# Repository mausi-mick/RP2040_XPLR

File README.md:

VL53L0X 360° Radar mit RP2040 auf Experimentierboard

Aufgebaut habe ich das „Radar" auf einem von mir entwickelten Experimentierboard für den RP2040 bzw. RP2350 im Format 100 x 160:

Auf dem Board - neben dem PICO-Board - können folgende Komponeneten eingesteckt werden :

    SPI - (Touch) - Displays mit ILI9341 Treiber von 2.4 bis 3.2 Zoll (240 x 320 Pixel)

                         und mit ST7736 Treiber      3.5 und 4 Zoll   (320 x 480 Pixel)

    Dual DAC MCP48x2 (8/10/12 bit) (SPI)
    Quad ADC MCP3x04 (10/12 bit)   (SPI)
    EEPROM 24LC64/256 (I2C)
    bis zu vier Encoder bzw. Potis
    vier Taster
    vier Steckplätze für LEDs

obige Komponenten sind auf Buchsen (Pinheader) steckbar.

Ausserdem ist das Boardmit einem kleinen Breadboard bestückt.

Die Stromversorgung erfolgt momentan über die USB-Buchse des Picos,
eine zusätzliche ist auf dem Board integrierbar (USBC) (-5V/60mA, 12V (ca 2A ).

Um möglichst viele dieser Komponenten zu testen, hab ich dieses Radar auf dem Board aufgebaut.

Es besteht aus zwei VL53L0X, die mit der Rückseite zueinander auf einem kleinen Servo (SG90?) befestigt sind.

Den Drehwinkel kann man mit der Software in geringen Grenzen ändern (hier: auf 180° justieren).

Das Programm ist in der Arduino IDE (2.34) erstellt.

Für die Grafik verwende ich die hervorragende Bibliothek TFT_eSPI von H. Bodmer,

für die Distanzsensoren die Bibliothek VL53L0X.h von Pololu.

Am Anfang läuft nur in rasendem Tempo der Grafik - Test ab.

Anschliessend wird der kreisförmige Radar-Bildschirm mit den Koordinaten angezeigt. Die Distanz-Sensoren nehmen ihre Arbeit auf und das Servo dreht sich von 0° - 180° und zurück...

Die Auflösung (maximale Entfernungsanzeige ) der Graphik lässt sich mit dem Drehencoder in

Stufen von 500 mm, 1000mm, 1500 mm und 2000 mm einstellen.

Löschung des Bildschirms geschieht über den RUN (=Reset)-Pin des Pico über Taster S2.

Das Programm und die Platinen-Layouts (KiCad) werden auf Github gestellt. Es gibt auch ein

kleines KiCad-Projekt zur Beschriftung der PICO-Pins (zum Aufkleben auf dem PICO ) :

{width="17cm" height="6.93cm"}

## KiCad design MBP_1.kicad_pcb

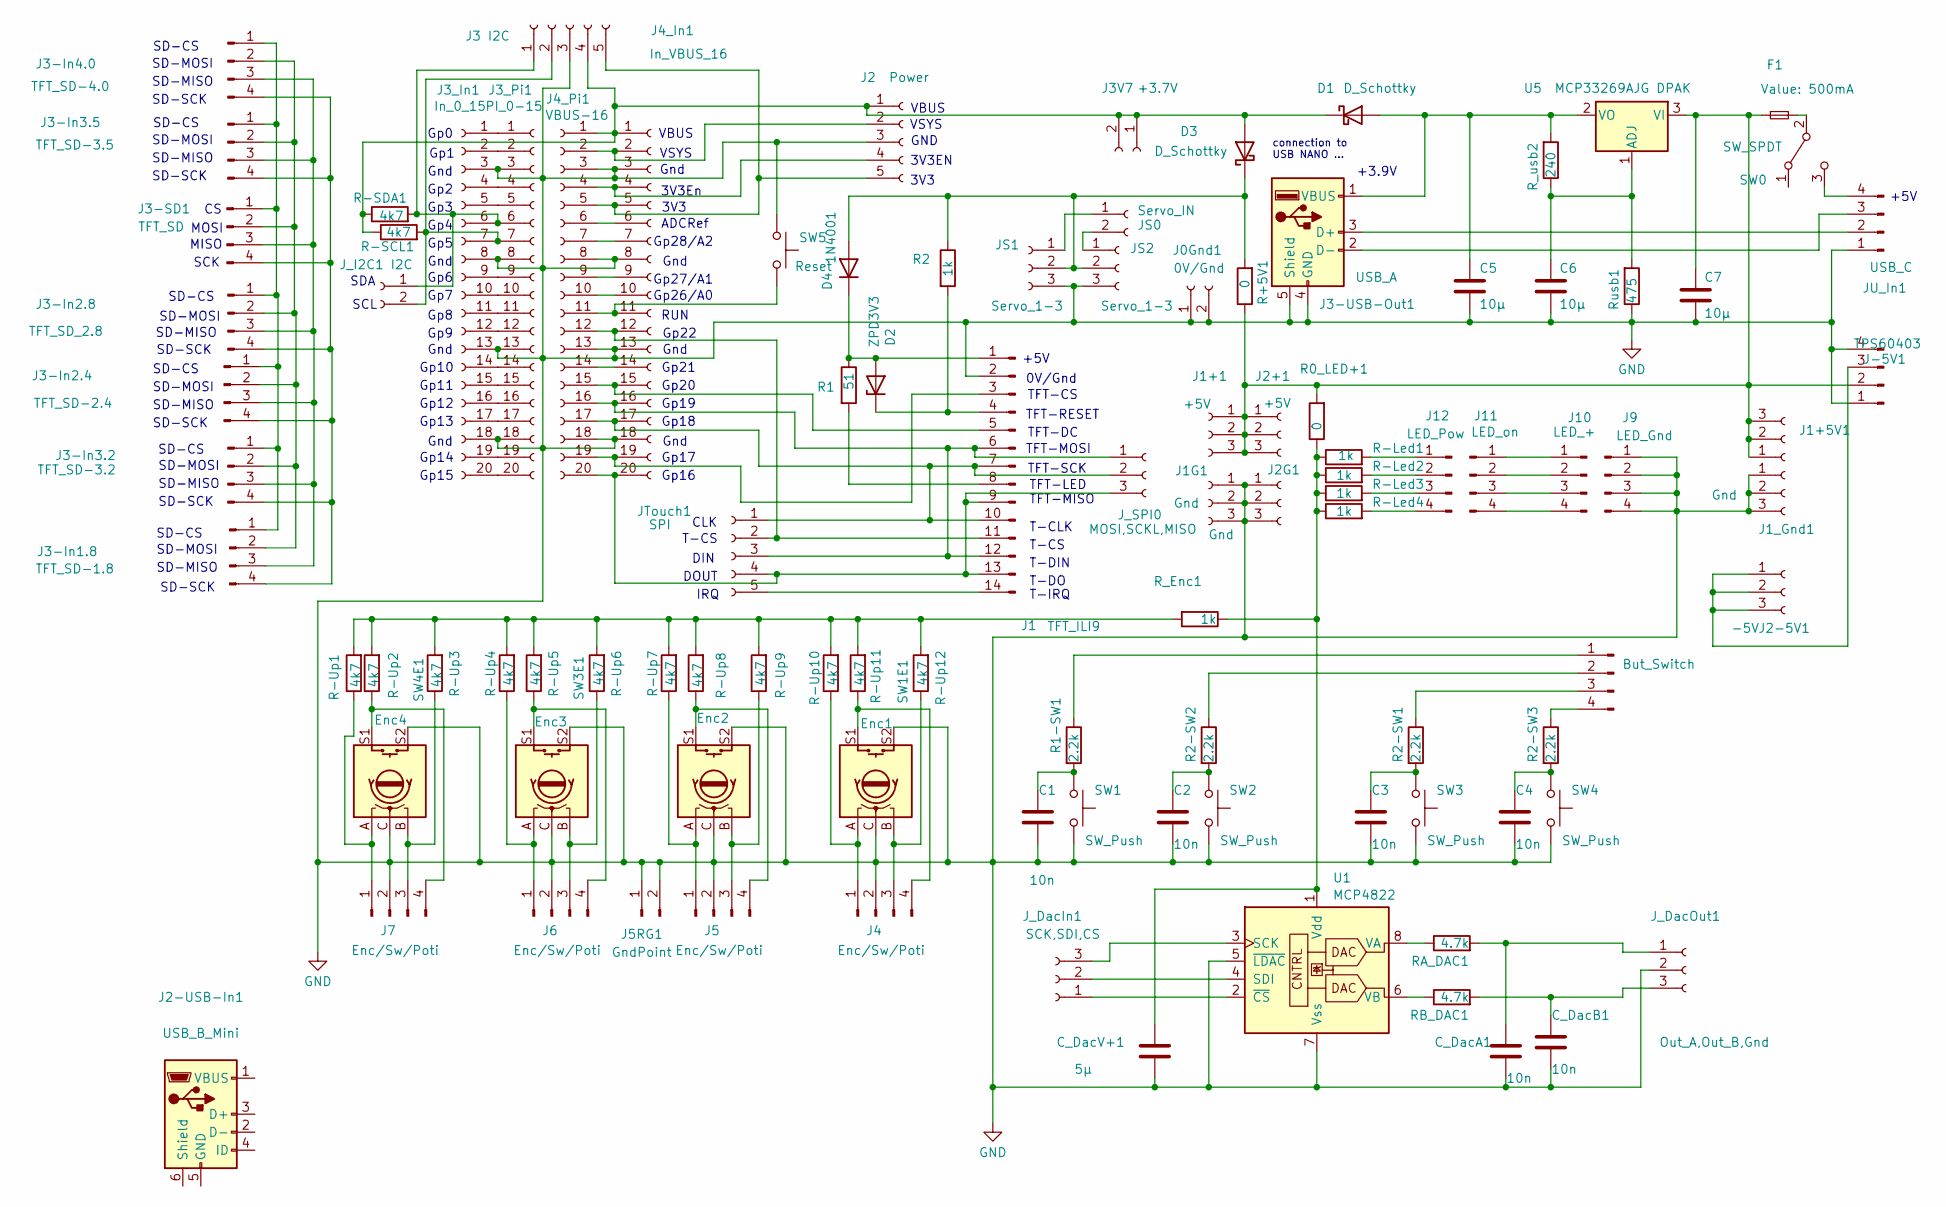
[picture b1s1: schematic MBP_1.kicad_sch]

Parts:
C1, C2, C3, C4: 10n; C_1206_3216Metric_Pad1.33x1.80mm_HandSolder
C5, C6, C7: 10µ; C_1812_4532Metric_Pad1.57x3.40mm_HandSolder
C_DacA1: 10n; C_1206_3216Metric_Pad1.33x1.80mm_HandSolder
C_DacB1: 10n; C_1206_3216Metric_Pad1.33x1.80mm_HandSolder
C_DacV+1: 5µ; C_1812_4532Metric_Pad1.57x3.40mm_HandSolder
D1: D_Schottky; D_DO-15_P15.24mm_Horizontal
D2: ZPD3V3; D_DO-35_SOD27_P10.16mm_Horizontal
D3: D_Schottky; D_DO-15_P12.70mm_Horizontal
D4: 1N4001; D_2010_5025Metric_Pad1.52x2.65mm_HandSolder
F1: 500mA; Fuse_2010_5025Metric_Pad1.52x2.65mm_HandSolder
J0Gnd1: 0V/Gnd; PinHeader_1x02_P2.54mm_Vertical
J1: TFT_ILI9; PinHeader_1x14_P2.54mm_Vertical
J1+1, J1+5V1, J2+1: +5V; PinHeader_1x03_P2.54mm_Vertical
J1G1, J1_Gnd1, J2G1: Gnd; PinHeader_1x03_P2.54mm_Vertical
J2: Power; PinSocket_1x05_P2.54mm_Vertical
J2-5V1: -5V; PinHeader_1x03_P2.54mm_Vertical
J2-USB-In1: USB_B_Mini; USB_Mini-B_Wuerth_65100516121_Horizontal
J3: I2C; PinSocket_1x05_P2.54mm_Vertical
J3-In1.8: TFT_SD-1.8; PinHeader_1x04_P2.54mm_Vertical
J3-In2.4: TFT_SD-2.4; PinHeader_1x04_P2.54mm_Vertical
J3-In2.8: TFT_SD_2.8; PinSocket_1x04_P2.54mm_Vertical
J3-In3.2: TFT_SD-3.2; PinHeader_1x04_P2.54mm_Vertical
J3-In3.5: TFT_SD-3.5; PinHeader_1x04_P2.54mm_Vertical
J3-In4.0: TFT_SD-4.0; PinHeader_1x04_P2.54mm_Vertical
J3-SD1: TFT_SD; PinHeader_1x04_P2.54mm_Horizontal
J3-USB-Out1: USB_A; USB_A_Stewart_SS-52100-001_Horizontal
J3V7: +3.7V; PinHeader_1x02_P2.54mm_Vertical
J3_In1: In_0_15; PinSocket_1x20_P2.54mm_Vertical
J3_Pi1: PI_0-15; PinSocket_1x20_P2.54mm_Vertical
J4, J5, J6, J7: Enc/Sw/Poti; PinHeader_1x04_P2.54mm_Vertical
J4_In1: In_VBUS_16; PinSocket_1x20_P2.54mm_Vertical
J4_Pi1: VBUS-16; PinSocket_1x20_P2.54mm_Vertical
J5RG1: GndPoint; PinHeader_1x02_P2.54mm_Vertical
J8: But_Switch; PinHeader_1x04_P2.54mm_Vertical
J9: LED_Gnd; PinHeader_1x04_P2.54mm_Vertical
J10: LED_+; PinHeader_1x04_P2.54mm_Vertical
J11: LED_on; PinHeader_1x04_P2.54mm_Vertical
J12: LED_Pow; PinHeader_1x04_P2.54mm_Vertical
J-5V1: TPS60403; PinHeader_1x04_P2.54mm_Vertical
JS0: Servo_IN; PinSocket_1x02_P2.54mm_Vertical
JS1, JS2: Servo_1-3; PinHeader_1x03_P2.54mm_Vertical
JTouch1: SPI; PinHeader_1x05_P2.54mm_Vertical
JU_In1: USB_C; PinHeader_1x04_P2.54mm_Vertical
J_DacIn1: SCK,SDI,CS; PinHeader_1x03_P2.54mm_Vertical
J_DacOut1: Out_A,Out_B,Gnd; PinHeader_1x03_P2.54mm_Vertical
J_I2C1: I2C; PinSocket_1x02_P2.54mm_Vertical
J_SPI0: MOSI,SCKL,MISO; PinHeader_1x03_P2.54mm_Vertical
R0_LED+1: 0; R_Axial_DIN0207_L6.3mm_D2.5mm_P10.16mm_Horizontal
R1: 51; R_Axial_DIN0207_L6.3mm_D2.5mm_P10.16mm_Horizontal
R1-SW1, R2-SW1, R2-SW2, R2-SW3: 2.2k; R_1206_3216Metric_Pad1.30x1.75mm_HandSolder
R2: 1k; R_Axial_DIN0207_L6.3mm_D2.5mm_P10.16mm_Horizontal
R+5V1: 0; R_Axial_DIN0207_L6.3mm_D2.5mm_P10.16mm_Horizontal
R-Led1, R-Led2, R-Led3, R-Led4: 1k; R_1206_3216Metric_Pad1.30x1.75mm_HandSolder
R-SCL1: 4k7; R_1206_3216Metric_Pad1.30x1.75mm_HandSolder
R-SDA1: 4k7; R_1206_3216Metric_Pad1.30x1.75mm_HandSolder
R-Up1, R-Up2, R-Up3, R-Up4, R-Up5, R-Up6, R-Up7, R-Up8, R-Up9, R-Up10, R-Up11, R-Up12: 4k7; R_1206_3216Metric_Pad1.30x1.75mm_HandSolder
RA_DAC1: 4.7k; R_1206_3216Metric_Pad1.30x1.75mm_HandSolder
RB_DAC1: 4.7k; R_1206_3216Metric_Pad1.30x1.75mm_HandSolder
R_Enc1: 1k; R_Axial_DIN0207_L6.3mm_D2.5mm_P10.16mm_Horizontal
R_usb2: 240; R_Axial_DIN0207_L6.3mm_D2.5mm_P10.16mm_Horizontal
Rusb1: 475; R_Axial_DIN0207_L6.3mm_D2.5mm_P10.16mm_Horizontal
SW0: SW_SPDT; Molex_KK-396_5273-03A_1x03_P3.96mm_Vertical
SW1, SW2, SW3, SW4: SW_Push; SW_PUSH_6mm_H7.3mm
SW1E1: Enc1; RotaryEncoder_Alps_EC11E-Switch_Vertical_H20mm
SW2E1: Enc2; RotaryEncoder_Alps_EC11E-Switch_Vertical_H20mm
SW3E1: Enc3; RotaryEncoder_Alps_EC11E-Switch_Vertical_H20mm
SW4E1: Enc4; RotaryEncoder_Alps_EC11E-Switch_Vertical_H20mm
SW5: Reset; SW_PUSH_6mm_H7.3mm
U1: MCP4822; DIP-8_W7.62mm_LongPads
U5: MCP33269AJG DPAK; ATPAK-2

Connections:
GND: C1.2, C2.2, C3.2, C4.2, C5.2, C6.2, C7.2, C_DacA1.2, C_DacB1.2, C_DacV+1.2, J0Gnd1.1, J0Gnd1.2, J1.2, J1G1.1, J1G1.2, J1G1.3, J1_Gnd1.1, J1_Gnd1.2, J1_Gnd1.3, J2.3, J2G1.1, J2G1.2, J2G1.3, J3.3, J3-USB-Out1.4 (GND), J3-USB-Out1.5 (Shield), J3_In1.3, J3_In1.8, J3_In1.13, J3_In1.18, J3_Pi1.3, J3_Pi1.8, J3_Pi1.13, J3_Pi1.18, J4.2, J4_In1.3, J4_In1.8, J4_In1.13, J4_In1.18, J4_Pi1.3, J4_Pi1.8, J4_Pi1.13, J4_Pi1.18, J5.2, J5RG1.1, J5RG1.2, J6.2, J7.2, J9.1, J9.2, J9.3, J9.4, J-5V1.1, J-5V1.4, JS1.3, JS2.3, JU_In1.1, J_DacOut1.2, Rusb1.1, SW1.1, SW1E1.C, SW1E1.S2, SW2.1, SW2E1.C, SW2E1.S2, SW3.1, SW3E1.C, SW3E1.S2, SW4.1, SW4E1.C, SW4E1.S2, SW5.2, U1.5 (~LDAC), U1.7 (Vss)
unnamed: C1.1, R1-SW1.2, SW1.2
unnamed: C2.1, R2-SW2.2, SW2.2
unnamed: C3.1, R2-SW1.2, SW3.2
unnamed: C4.1, R2-SW3.2, SW4.2
unnamed: C5.1, D1.2 (A), J3-USB-Out1.1 (VBUS), R_usb2.2, U5.2 (VO)
unnamed: D1.1 (K), D3.2 (A), J2.1, J3.4, J3V7.1, J3V7.2, J4_In1.1, J4_Pi1.1, R-SCL1.1, R-SDA1.1
unnamed: D2.2 (A), D4.1 (K), J1.1, R1.1
unnamed: D2.1 (K), J1.4, R2.2
unnamed: D3.1 (K), D4.2 (A), JS1.2, JS2.2, R2.1, R+5V1.2
unnamed: J1.3, J4_In1.19, J4_Pi1.19
unnamed: J1.5, J4_In1.15, J4_Pi1.15
unnamed: J1.8, R1.2
unnamed: J1.7, J1.10, J4_In1.17, J4_Pi1.17, JTouch1.1, J_SPI0.2
unnamed: J1.11, J4_In1.12, J4_Pi1.12, JTouch1.2
unnamed: J1.6, J1.12, J4_In1.16, J4_Pi1.16, JTouch1.3, J_SPI0.1
unnamed: J1.9, J1.13, J4_In1.20, J4_Pi1.20, JTouch1.4, J_SPI0.3
unnamed: J1.14, JTouch1.5
unnamed: J2.2, J4_In1.2, J4_Pi1.2
unnamed: J2.4, J4_In1.4, J4_Pi1.4
unnamed: J2.5, J3.5, J4_In1.5, J4_Pi1.5
unnamed: J3-In1.8.1, J3-In2.4.1, J3-In2.8.1, J3-In3.2.1, J3-In3.5.1, J3-In4.0.1, J3-SD1.1
unnamed: J3-In1.8.2, J3-In2.4.2, J3-In2.8.2, J3-In3.2.2, J3-In3.5.2, J3-In4.0.2, J3-SD1.2
unnamed: J3-In1.8.3, J3-In2.4.3, J3-In2.8.3, J3-In3.2.3, J3-In3.5.3, J3-In4.0.3, J3-SD1.3
unnamed: J3-In1.8.4, J3-In2.4.4, J3-In2.8.4, J3-In3.2.4, J3-In3.5.4, J3-In4.0.4, J3-SD1.4
unnamed: J3.1, J3_In1.6, J3_Pi1.6, J_I2C1.1, R-SDA1.2
unnamed: J3.2, J3_In1.7, J3_Pi1.7, J_I2C1.2, R-SCL1.2
unnamed: J3-USB-Out1.3 (D+), JU_In1.2
unnamed: J3-USB-Out1.2 (D-), JU_In1.3
unnamed: J3_In1.1, J3_Pi1.1
unnamed: J3_In1.2, J3_Pi1.2
unnamed: J3_In1.4, J3_Pi1.4
unnamed: J3_In1.5, J3_Pi1.5
unnamed: J3_In1.9, J3_Pi1.9
unnamed: J3_In1.10, J3_Pi1.10
unnamed: J3_In1.11, J3_Pi1.11
unnamed: J3_In1.12, J3_Pi1.12
unnamed: J3_In1.14, J3_Pi1.14
unnamed: J3_In1.15, J3_Pi1.15
unnamed: J3_In1.16, J3_Pi1.16
unnamed: J3_In1.17, J3_Pi1.17
unnamed: J3_In1.19, J3_Pi1.19
unnamed: J3_In1.20, J3_Pi1.20
unnamed: J4.1, R-Up10.1, SW1E1.A
unnamed: J4.3, R-Up12.1, SW1E1.B
unnamed: J4.4, R-Up11.1, SW1E1.S1
unnamed: J4_In1.6, J4_Pi1.6
unnamed: J4_In1.7, J4_Pi1.7
unnamed: J4_In1.9, J4_Pi1.9
unnamed: J4_In1.10, J4_Pi1.10
unnamed: J4_In1.11, J4_Pi1.11, SW5.1
unnamed: J4_In1.14, J4_Pi1.14
unnamed: J5.1, R-Up7.1, SW2E1.A
unnamed: J5.3, R-Up9.1, SW2E1.B
unnamed: J5.4, R-Up8.1, SW2E1.S1
unnamed: J6.1, R-Up4.1, SW3E1.A
unnamed: J6.3, R-Up6.1, SW3E1.B
unnamed: J6.4, R-Up5.1, SW3E1.S1
unnamed: J7.1, R-Up1.1, SW4E1.A
unnamed: J7.3, R-Up3.1, SW4E1.B
unnamed: J7.4, R-Up2.1, SW4E1.S1
unnamed: J8.1, R1-SW1.1
unnamed: J8.2, R2-SW2.1
unnamed: J8.3, R2-SW1.1
unnamed: J8.4, R2-SW3.1
unnamed: J10.1, J11.1
unnamed: J10.2, J11.2
unnamed: J10.3, J11.3
unnamed: J10.4, J11.4
unnamed: J12.1, R-Led1.2
unnamed: J12.2, R-Led2.2
unnamed: J12.3, R-Led3.2
unnamed: J12.4, R-Led4.2
unnamed: C7.1, F1.1, J1+1.1, J1+1.2, J1+1.3, J1+5V1.1, J1+5V1.2, J1+5V1.3, J2+1.1, J2+1.2, J2+1.3, J-5V1.2, R0_LED+1.2, R+5V1.1, U5.3 (VI)
unnamed: J2-5V1.1, J2-5V1.2, J2-5V1.3, J-5V1.3
unnamed: JS0.1, JS1.1
unnamed: JS0.2, JS2.1
unnamed: JU_In1.4, SW0.3 (C)
unnamed: J_DacIn1.1, U1.2 (~CS)
unnamed: J_DacIn1.2, U1.4 (SDI)
unnamed: J_DacIn1.3, U1.3 (SCK)
unnamed: C_DacA1.1, J_DacOut1.1, RA_DAC1.2
unnamed: C_DacB1.1, J_DacOut1.3, RB_DAC1.2
unnamed: R-Up1.2, R-Up2.2, R-Up3.2, R-Up4.2, R-Up5.2, R-Up6.2, R-Up7.2, R-Up8.2, R-Up9.2, R-Up10.2, R-Up11.2, R-Up12.2, R_Enc1.2
unnamed: F1.2, SW0.2 (B)
unnamed: RA_DAC1.1, U1.8 (VA)
unnamed: RB_DAC1.1, U1.6 (VB)
unnamed: C_DacV+1.1, R0_LED+1.1, R-Led1.1, R-Led2.1, R-Led3.1, R-Led4.1, R_Enc1.1, U1.1 (Vdd)
unnamed: C6.1, R_usb2.1, Rusb1.2, U5.1 (ADJ)

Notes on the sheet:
Gp19
CLK
SD-CS
SD-MISO
Gp13
MISO
RUN
SD-MOSI
0V/Gnd
Gp16
Gp20
DIN
Gnd
DOUT
Gp18
3V3EN
Gp15
Gp5
ADCRef
TFT-LED
T-CS
TFT-RESET
TFT-DC
Gp21
Gp11
Gp9
Gp6
VSYS
3V3
Gp14
TFT-CS
T-CLK
Gp0
Gp12
Gp10
MOSI
T-DIN
Gp7
connection to USB NANO ...
+5V

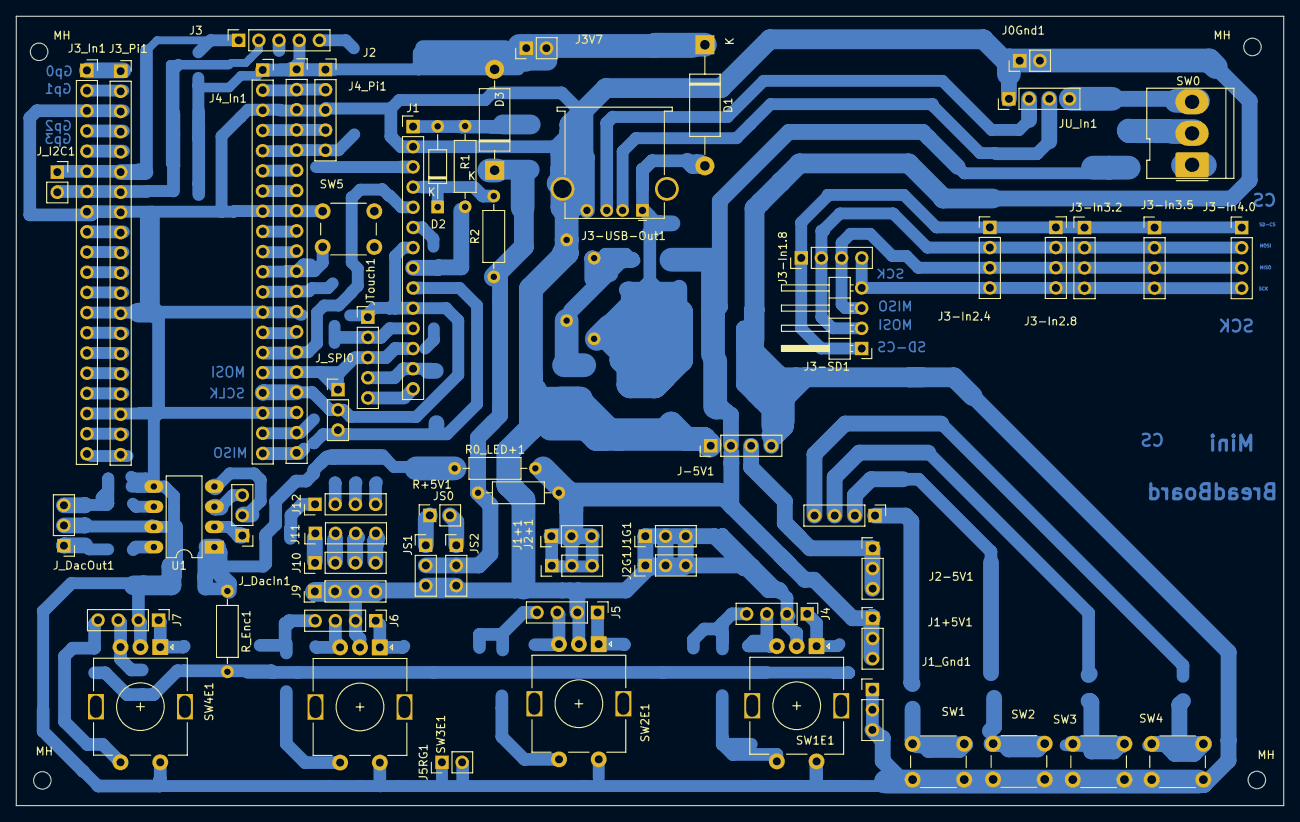
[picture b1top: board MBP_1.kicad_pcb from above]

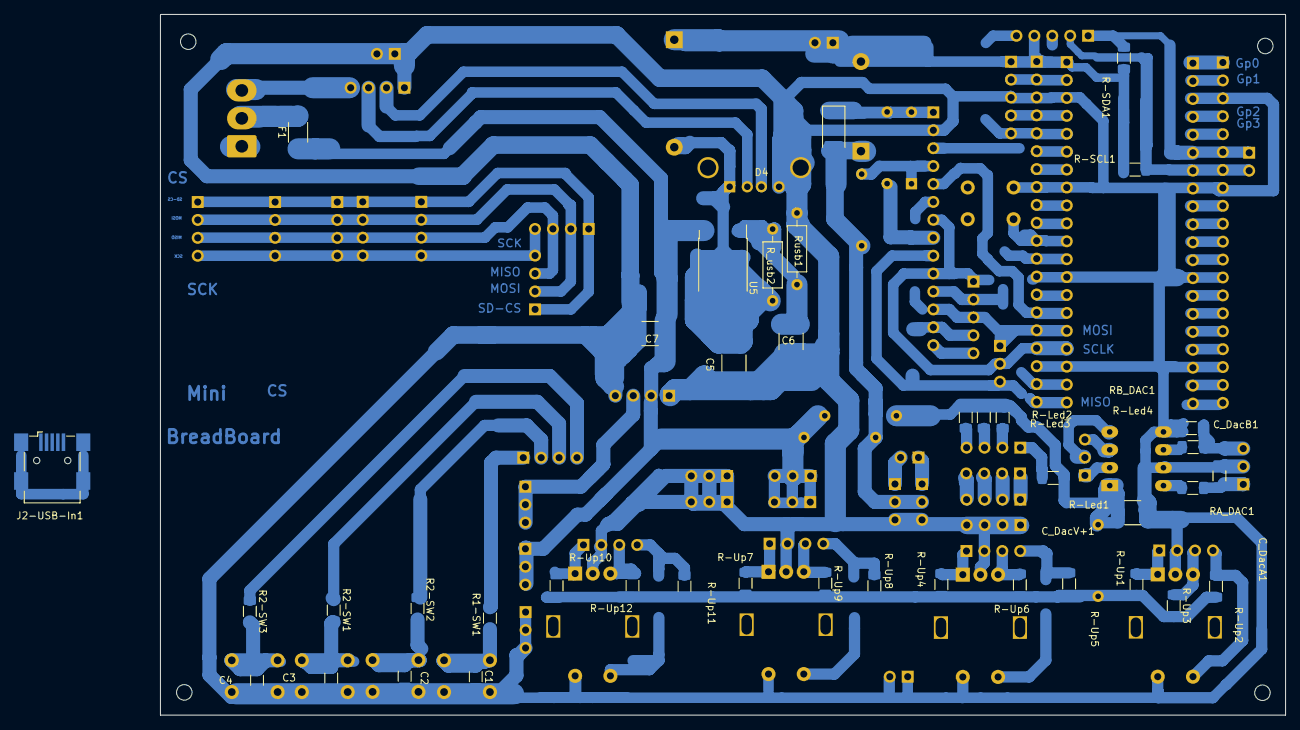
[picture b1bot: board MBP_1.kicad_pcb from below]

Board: 2 copper layers, 159.5 x 99.3 mm, 107 parts (40 on the bottom side), 89 nets.

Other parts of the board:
MH: MH_2.2; MountingHole_2.2mm_M2_DIN965
MH#2, MH#3, MH#4: MH_2.2; MountingHole_2.2mm_M2_DIN965

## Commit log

2025-02-11 Rename README.md to README_pic.md
